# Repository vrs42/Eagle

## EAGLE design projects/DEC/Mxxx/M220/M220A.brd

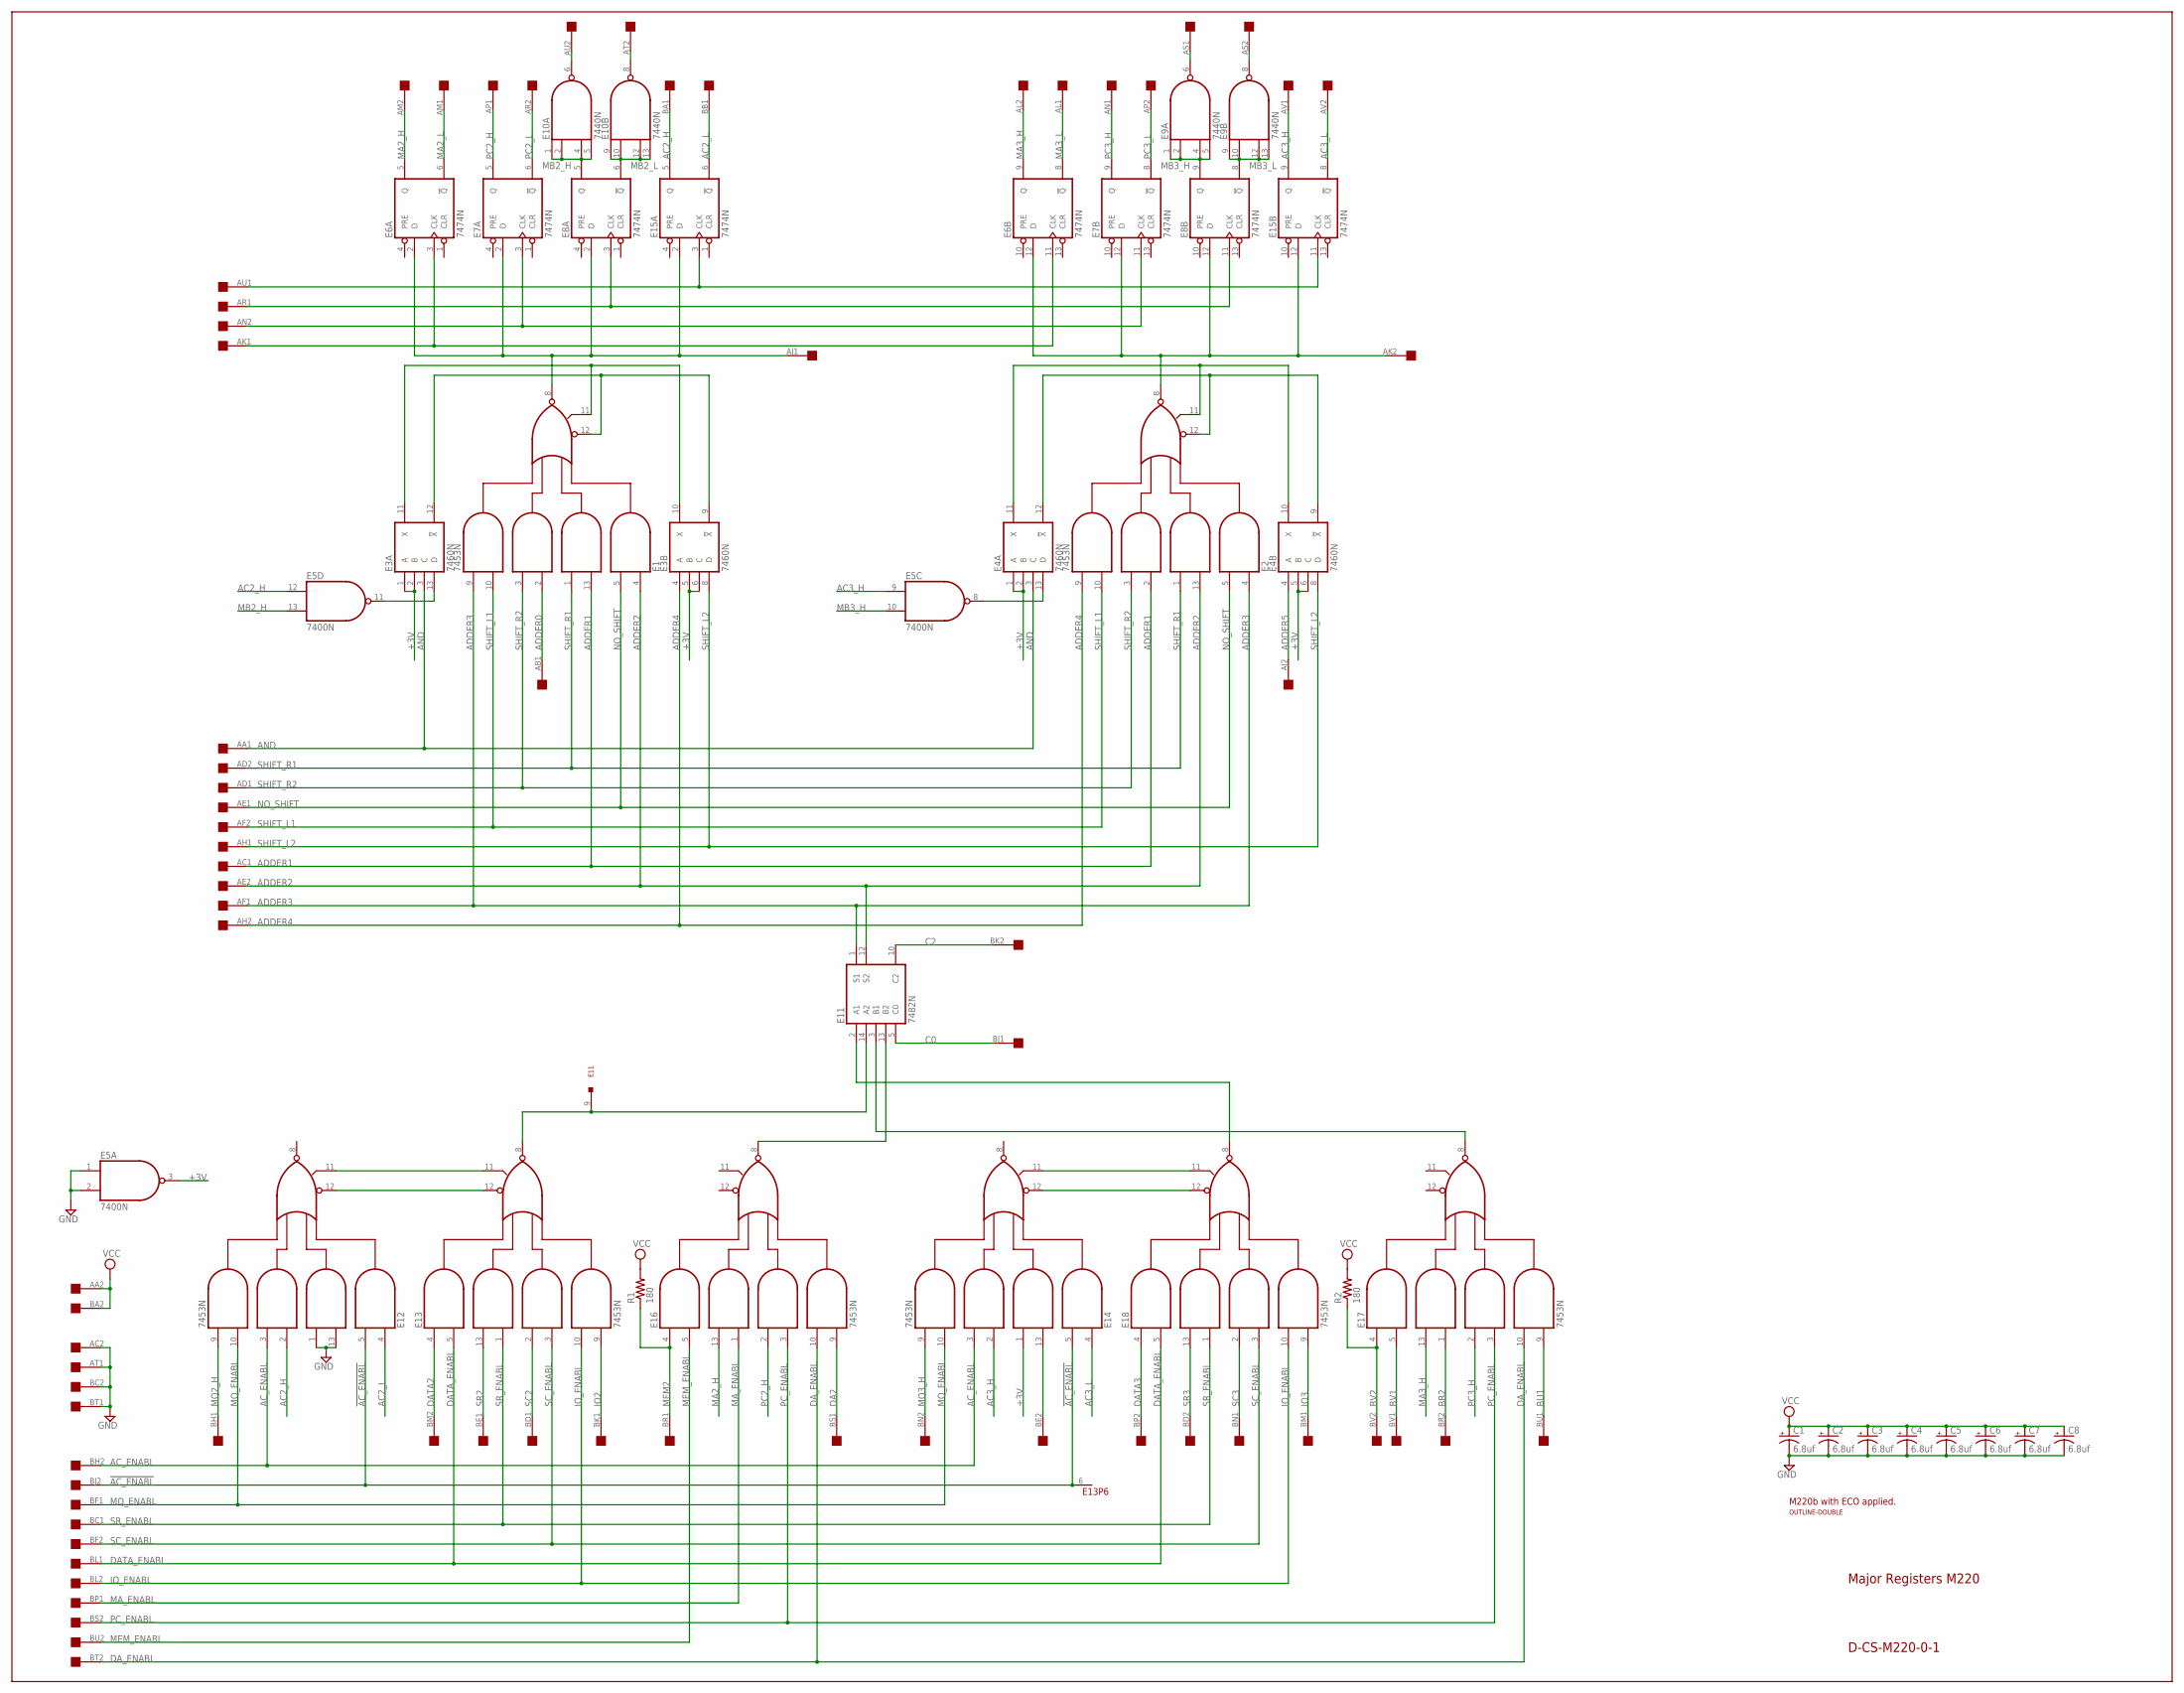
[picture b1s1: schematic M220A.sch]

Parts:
C1, C2, C3, C4, C5, C6, C7, C8: 6.8uf; E15-5
E1, E2, E12, E13, E14, E16, E17, E18: 7453N; DIL14
E3, E4: 7460N; DIL14
E5: 7400N; DIL14
E6, E7, E8, E15: 7474N; DIL14
E9, E10: 7440N; DIL14
E11: 7482N; DIL14
R1, R2: 180; 0207/10
U$1: DOUBLE; EDGE-CON4
U$2: OUTLINE-DOUBLE; DOUBLE

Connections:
!AC_ENABL: E12.5 (I2), E13.6 (SPARE), E14.5 (I2), U$1.BJ2
+3V: E3.1 (A), E3.2 (B), E3.5 (B), E3.6 (C), E4.1 (A), E4.2 (B), E4.5 (B), E4.6 (C), E5.3 (O), E14.1 (I4)
AC2_H: E5.12 (I0), E12.2 (I5), E15.5 (Q), U$1.BA1
AC2_L: E12.4 (I1), E15.6 (!Q), U$1.BB1
AC3_H: E5.9 (I0), E14.2 (I5), E15.9 (Q), U$1.AV1
AC3_L: E14.4 (I1), E15.8 (!Q), U$1.AV2
AC_ENABL: E12.3 (I6), E14.3 (I6), U$1.BH2
ADDER0: E1.2 (I5), U$1.AB1
ADDER1: E1.13 (I3), E2.2 (I5), U$1.AC1
ADDER2: E1.4 (I1), E2.13 (I3), E11.12 (S2), U$1.AE2
ADDER3: E1.9 (I8), E2.4 (I1), E11.1 (S1), U$1.AF1
ADDER4: E2.9 (I8), E3.4 (A), U$1.AH2
ADDER5: E4.4 (A), U$1.AJ2
AJ1: E1.8 (O), E6.2 (D), E7.2 (D), E8.2 (D), E15.2 (D), U$1.AJ1
AK1: E6.3 (CLK), E6.11 (CLK), U$1.AK1
AK2: E2.8 (O), E6.12 (D), E7.12 (D), E8.12 (D), E15.12 (D), U$1.AK2
AN2: E7.3 (CLK), E7.11 (CLK), U$1.AN2
AND: E3.3 (C), E4.3 (C), U$1.AA1
AR1: E8.3 (CLK), E8.11 (CLK), U$1.AR1
AS2: E9.8 (O), U$1.AS2
AT2: E10.8 (O), U$1.AT2
AU1: E15.3 (CLK), E15.11 (CLK), U$1.AU1
AU2: E10.6 (O), U$1.AU2
BE2: E14.13 (I3), U$1.BE2
BR2: E17.1 (I4), U$1.BR2
BU1: E17.9 (I8), U$1.BU1
BV1: E17.5 (I2), U$1.BV1
BV2: E17.4 (I1), R2.1, U$1.BV2
C0: E11.5 (C0), U$1.BJ1
C2: E11.10 (C2), U$1.BK2
DA2: E16.9 (I8), U$1.BS1
DATA2: E13.4 (I1), U$1.BM2
DATA3: E18.4 (I1), U$1.BP2
DATA_ENABL: E13.5 (I2), E18.5 (I2), U$1.BL1
DA_ENABL: E16.10 (I7), E17.10 (I7), U$1.BT2
GND: C1.-, C2.-, C3.-, C4.-, C5.-, C6.-, C7.-, C8.-, E1.7 (GND), E2.7 (GND), E3.7 (GND), E4.7 (GND), E5.1 (I0), E5.2 (I1), E5.7 (GND), E6.7 (GND), E7.7 (GND), E8.7 (GND), E9.7 (GND), E10.7 (GND), E11.11 (GND), E12.1 (I4), E12.7 (GND), E12.13 (I3), E13.7 (GND), E14.7 (GND), E15.7 (GND), E16.7 (GND), E17.7 (GND), E18.7 (GND), U$1.AC2, U$1.AT1, U$1.BC2, U$1.BT1
IO2: E13.9 (I8), U$1.BK1
IO3: E18.9 (I8), U$1.BM1
IO_ENABL: E13.10 (I7), E18.10 (I7), U$1.BL2
MA2_H: E6.5 (Q), E16.13 (I3), U$1.AM2
MA2_L: E6.6 (!Q), U$1.AM1
MA3_H: E6.9 (Q), E17.13 (I3), U$1.AL2
MA3_L: E6.8 (!Q), U$1.AL1
MA_ENABL: E16.1 (I4), U$1.BP1
MB2_H: E5.13 (I1), E8.5 (Q), E10.1 (I0), E10.2 (I1), E10.4 (I2), E10.5 (I3)
MB2_L: E8.6 (!Q), E10.9 (I0), E10.10 (I1), E10.12 (I2), E10.13 (I3)
MB3_H: E5.10 (I1), E8.9 (Q), E9.1 (I0), E9.2 (I1), E9.4 (I2), E9.5 (I3)
MB3_L: E8.8 (!Q), E9.9 (I0), E9.10 (I1), E9.12 (I2), E9.13 (I3)
MEM2: E16.4 (I1), R1.1, U$1.BR1
MEM_ENABL: E16.5 (I2), U$1.BU2
MQ2_H: E12.9 (I8), U$1.BH1
MQ3_H: E14.9 (I8), U$1.BN2
MQ_ENABL: E12.10 (I7), E14.10 (I7), U$1.BF1
unnamed: E3.13 (D), E5.11 (O)
unnamed: E14.12 (I9), E18.12 (I9)
unnamed: E4.13 (D), E5.8 (O)
unnamed: E14.11 (I10), E18.11 (I10)
unnamed: E11.9, E11.14 (A2), E13.8 (O)
unnamed: E12.11 (I10), E13.11 (I10)
unnamed: E12.12 (I9), E13.12 (I9)
unnamed: E11.2 (A1), E18.8 (O)
unnamed: E2.12 (I9), E4.9 (!X), E4.12 (!X)
unnamed: E1.12 (I9), E3.9 (!X), E3.12 (!X)
unnamed: E2.11 (I10), E4.10 (X), E4.11 (X)
unnamed: E11.13 (B2), E16.8 (O)
unnamed: E1.11 (I10), E3.10 (X), E3.11 (X)
unnamed: E11.3 (B1), E17.8 (O)
unnamed: E9.6 (O), U$1.AS1
NO_SHIFT: E1.5 (I2), E2.5 (I2), U$1.AE1
PC2_H: E7.5 (Q), E16.2 (I5), U$1.AP1
PC2_L: E7.6 (!Q), U$1.AR2
PC3_H: E7.9 (Q), E17.2 (I5), U$1.AN1
PC3_L: E7.8 (!Q), U$1.AP2
PC_ENABL: E16.3 (I6), E17.3 (I6), U$1.BS2
SC2: E13.2 (I5), U$1.BD1
SC3: E18.2 (I5), U$1.BN1
SC_ENABL: E13.3 (I6), E18.3 (I6), U$1.BF2
SHIFT_L1: E1.10 (I7), E2.10 (I7), U$1.AF2
SHIFT_L2: E3.8 (D), E4.8 (D), U$1.AH1
SHIFT_R1: E1.1 (I4), E2.1 (I4), U$1.AD2
SHIFT_R2: E1.3 (I6), E2.3 (I6), U$1.AD1
SR2: E13.13 (I3), U$1.BE1
SR3: E18.13 (I3), U$1.BD2
SR_ENABL: E13.1 (I4), E18.1 (I4), U$1.BC1
VCC: C1.+, C2.+, C3.+, C4.+, C5.+, C6.+, C7.+, C8.+, E1.14 (VCC), E2.14 (VCC), E3.14 (VCC), E4.14 (VCC), E5.14 (VCC), E6.14 (VCC), E7.14 (VCC), E8.14 (VCC), E9.14 (VCC), E10.14 (VCC), E11.4 (VCC), E12.14 (VCC), E13.14 (VCC), E14.14 (VCC), E15.14 (VCC), E16.14 (VCC), E17.14 (VCC), E18.14 (VCC), R1.2, R2.2, U$1.AA2, U$1.BA2

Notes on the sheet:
M220b with ECO applied.
Major Registers M220
D-CS-M220-0-1

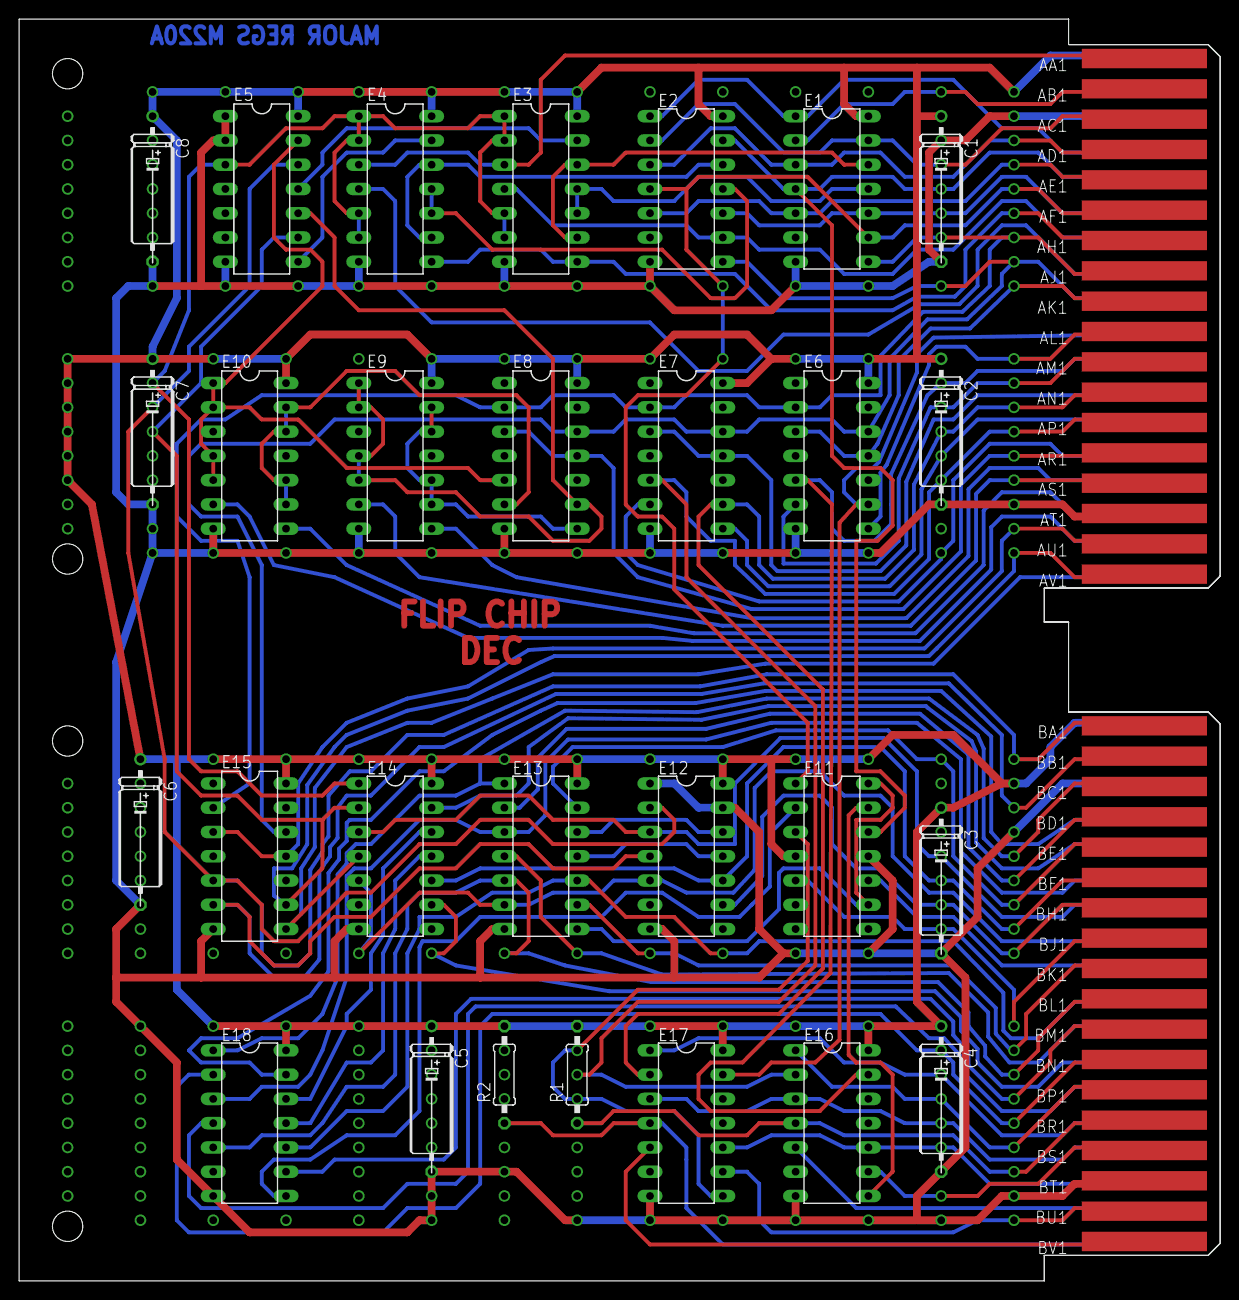
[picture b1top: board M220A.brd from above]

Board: 2 copper layers, 125.7 x 132.1 mm, 31 parts (0 on the bottom side), 85 nets.

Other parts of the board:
U$3: FLIPCHIP

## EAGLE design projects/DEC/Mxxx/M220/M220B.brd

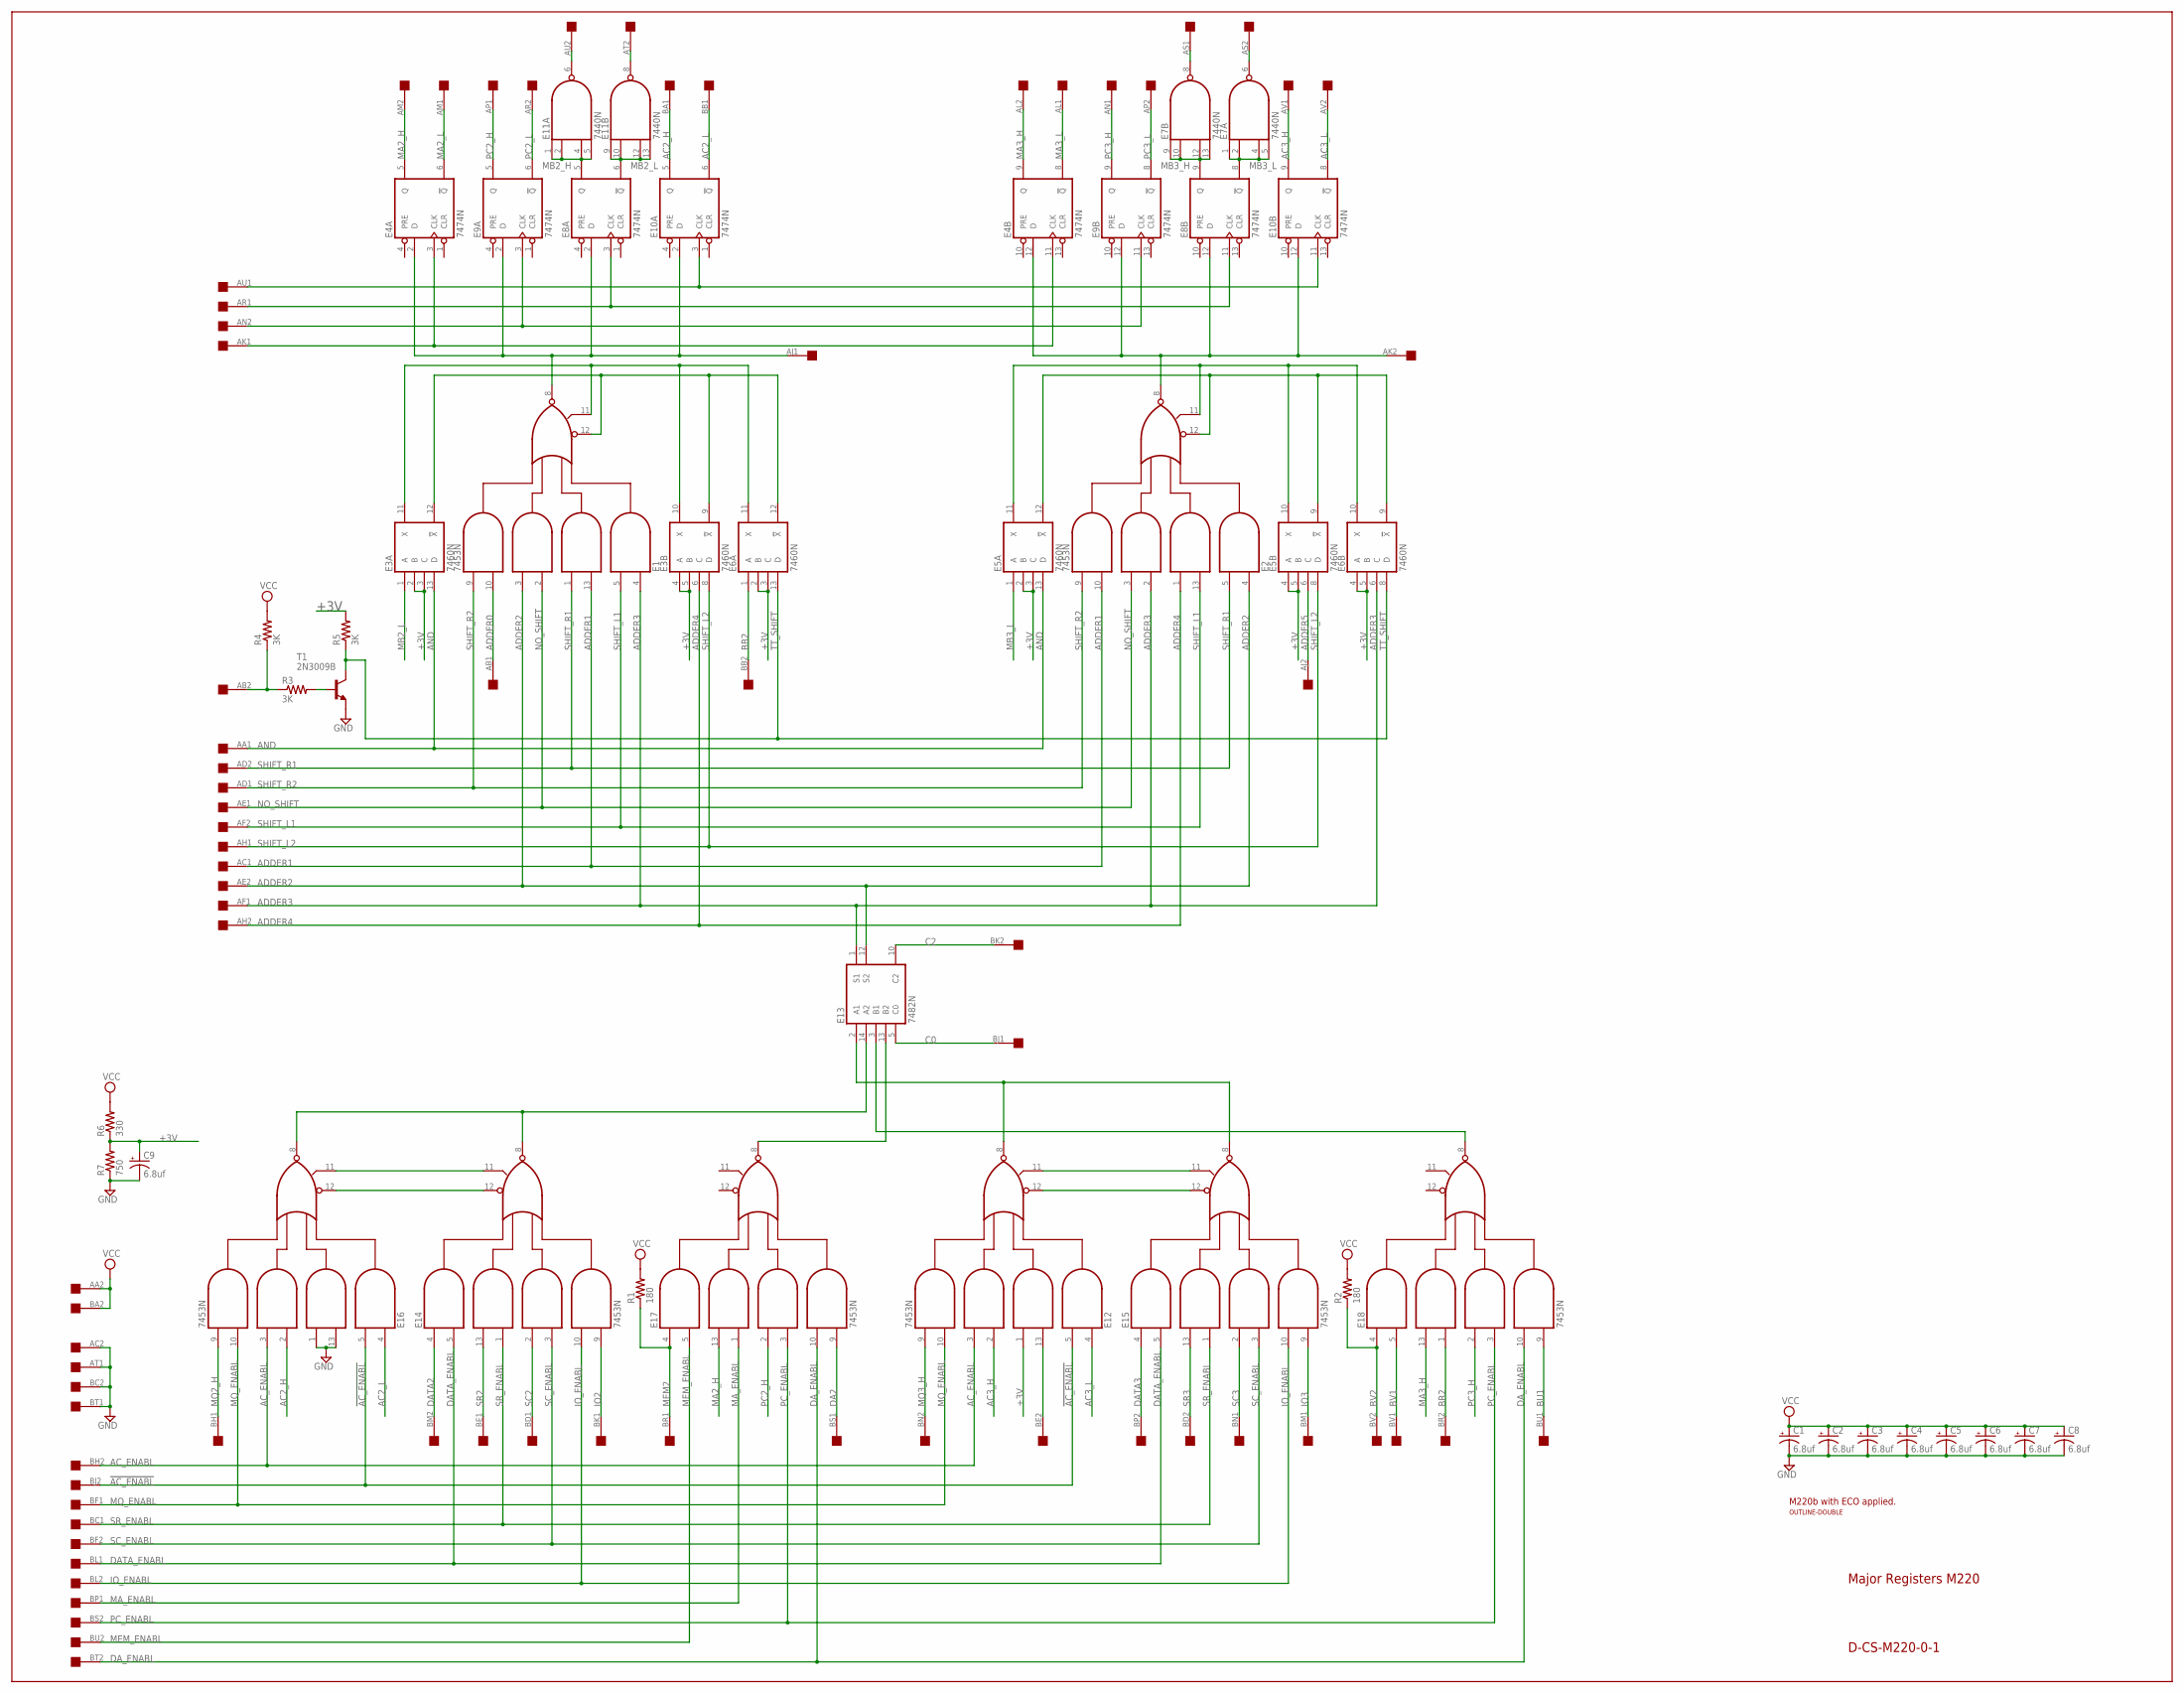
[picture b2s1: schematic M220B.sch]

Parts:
C1, C2, C3, C4, C5, C6, C7, C8, C9: 6.8uf; E15-5
E1, E2, E12, E14, E15, E16, E17, E18: 7453N; DIL14
E3, E5, E6: 7460N; DIL14
E4, E8, E9, E10: 7474N; DIL14
E7, E11: 7440N; DIL14
E13: 7482N; DIL14
R1, R2: 180; 0207/10
R3, R4, R5: 3K; 0207/10
R6: 330; 0207/10
R7: 750; 0207/10
T1: 2N3009B; TO5
U$1: DOUBLE; EDGE-CON4
U$2: OUTLINE-DOUBLE; DOUBLE

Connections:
!AC_ENABL: E12.5 (I2), E16.5 (I2), U$1.BJ2
!TT_SHIFT: R3.1, R4.1, U$1.AB2
+3V: C9.+, E3.2 (B), E3.3 (C), E3.4 (A), E3.5 (B), E5.2 (B), E5.3 (C), E5.4 (A), E5.5 (B), E6.2 (B), E6.3 (C), E6.4 (A), E6.5 (B), E12.1 (I4), R5.2, R6.1, R7.2
AC2_H: E10.5 (Q), E16.2 (I5), U$1.BA1
AC2_L: E10.6 (!Q), E16.4 (I1), U$1.BB1
AC3_H: E10.9 (Q), E12.2 (I5), U$1.AV1
AC3_L: E10.8 (!Q), E12.4 (I1), U$1.AV2
AC_ENABL: E12.3 (I6), E16.3 (I6), U$1.BH2
ADDER0: E1.10 (I7), U$1.AB1
ADDER1: E1.13 (I3), E2.10 (I7), U$1.AC1
ADDER2: E1.3 (I6), E2.4 (I1), E13.12 (S2), U$1.AE2
ADDER3: E1.4 (I1), E2.2 (I5), E6.6 (C), E13.1 (S1), U$1.AF1
ADDER4: E2.1 (I4), E3.6 (C), U$1.AH2
ADDER5: E5.6 (C), U$1.AJ2
AJ1: E1.8 (O), E4.2 (D), E8.2 (D), E9.2 (D), E10.2 (D), U$1.AJ1
AK1: E4.3 (CLK), E4.11 (CLK), U$1.AK1
AK2: E2.8 (O), E4.12 (D), E8.12 (D), E9.12 (D), E10.12 (D), U$1.AK2
AN2: E9.3 (CLK), E9.11 (CLK), U$1.AN2
AND: E3.13 (D), E5.13 (D), U$1.AA1
AR1: E8.3 (CLK), E8.11 (CLK), U$1.AR1
AS1: E7.8 (O), U$1.AS1
AS2: E7.6 (O), U$1.AS2
AT2: E11.8 (O), U$1.AT2
AU1: E10.3 (CLK), E10.11 (CLK), U$1.AU1
AU2: E11.6 (O), U$1.AU2
BB2: E6.1 (A), U$1.BB2
BE2: E12.13 (I3), U$1.BE2
BR2: E18.1 (I4), U$1.BR2
BU1: E18.9 (I8), U$1.BU1
BV1: E18.5 (I2), U$1.BV1
BV2: E18.4 (I1), R2.1, U$1.BV2
C0: E13.5 (C0), U$1.BJ1
C2: E13.10 (C2), U$1.BK2
DA2: E17.9 (I8), U$1.BS1
DATA2: E14.4 (I1), U$1.BM2
DATA3: E15.4 (I1), U$1.BP2
DATA_ENABL: E14.5 (I2), E15.5 (I2), U$1.BL1
DA_ENABL: E17.10 (I7), E18.10 (I7), U$1.BT2
GND: C1.-, C2.-, C3.-, C4.-, C5.-, C6.-, C7.-, C8.-, C9.-, E1.7 (GND), E2.7 (GND), E3.7 (GND), E4.7 (GND), E5.7 (GND), E6.7 (GND), E7.7 (GND), E8.7 (GND), E9.7 (GND), E10.7 (GND), E11.7 (GND), E12.7 (GND), E13.11 (GND), E14.7 (GND), E15.7 (GND), E16.1 (I4), E16.7 (GND), E16.13 (I3), E17.7 (GND), E18.7 (GND), R7.1, T1.1 (E), U$1.AC2, U$1.AT1, U$1.BC2, U$1.BT1
IO2: E14.9 (I8), U$1.BK1
IO3: E15.9 (I8), U$1.BM1
IO_ENABL: E14.10 (I7), E15.10 (I7), U$1.BL2
MA2_H: E4.5 (Q), E17.13 (I3), U$1.AM2
MA2_L: E4.6 (!Q), U$1.AM1
MA3_H: E4.9 (Q), E18.13 (I3), U$1.AL2
MA3_L: E4.8 (!Q), U$1.AL1
MA_ENABL: E17.1 (I4), U$1.BP1
MB2_H: E8.5 (Q), E11.1 (I0), E11.2 (I1), E11.4 (I2), E11.5 (I3)
MB2_L: E3.1 (A), E8.6 (!Q), E11.9 (I0), E11.10 (I1), E11.12 (I2), E11.13 (I3)
MB3_H: E7.9 (I0), E7.10 (I1), E7.12 (I2), E7.13 (I3), E8.9 (Q)
MB3_L: E5.1 (A), E7.1 (I0), E7.2 (I1), E7.4 (I2), E7.5 (I3), E8.8 (!Q)
MEM2: E17.4 (I1), R1.1, U$1.BR1
MEM_ENABL: E17.5 (I2), U$1.BU2
MQ2_H: E16.9 (I8), U$1.BH1
MQ3_H: E12.9 (I8), U$1.BN2
MQ_ENABL: E12.10 (I7), E16.10 (I7), U$1.BF1
unnamed: E12.12 (I9), E15.12 (I9)
unnamed: R3.2, T1.2 (B)
unnamed: E12.11 (I10), E15.11 (I10)
unnamed: E13.14 (A2), E14.8 (O), E16.8 (O)
unnamed: E14.11 (I10), E16.11 (I10)
unnamed: E14.12 (I9), E16.12 (I9)
unnamed: E12.8 (O), E13.2 (A1), E15.8 (O)
unnamed: E2.12 (I9), E5.9 (!X), E5.12 (!X), E6.9 (!X)
unnamed: E1.12 (I9), E3.9 (!X), E3.12 (!X), E6.12 (!X)
unnamed: E2.11 (I10), E5.10 (X), E5.11 (X), E6.10 (X)
unnamed: E13.13 (B2), E17.8 (O)
unnamed: E1.11 (I10), E3.10 (X), E3.11 (X), E6.11 (X)
unnamed: E13.3 (B1), E18.8 (O)
NO_SHIFT: E1.2 (I5), E2.3 (I6), U$1.AE1
PC2_H: E9.5 (Q), E17.2 (I5), U$1.AP1
PC2_L: E9.6 (!Q), U$1.AR2
PC3_H: E9.9 (Q), E18.2 (I5), U$1.AN1
PC3_L: E9.8 (!Q), U$1.AP2
PC_ENABL: E17.3 (I6), E18.3 (I6), U$1.BS2
SC2: E14.2 (I5), U$1.BD1
SC3: E15.2 (I5), U$1.BN1
SC_ENABL: E14.3 (I6), E15.3 (I6), U$1.BF2
SHIFT_L1: E1.5 (I2), E2.13 (I3), U$1.AF2
SHIFT_L2: E3.8 (D), E5.8 (D), U$1.AH1
SHIFT_R1: E1.1 (I4), E2.5 (I2), U$1.AD2
SHIFT_R2: E1.9 (I8), E2.9 (I8), U$1.AD1
SR2: E14.13 (I3), U$1.BE1
SR3: E15.13 (I3), U$1.BD2
SR_ENABL: E14.1 (I4), E15.1 (I4), U$1.BC1
TT_SHIFT: E6.8 (D), E6.13 (D), R5.1, T1.3 (C)
VCC: C1.+, C2.+, C3.+, C4.+, C5.+, C6.+, C7.+, C8.+, E1.14 (VCC), E2.14 (VCC), E3.14 (VCC), E4.14 (VCC), E5.14 (VCC), E6.14 (VCC), E7.14 (VCC), E8.14 (VCC), E9.14 (VCC), E10.14 (VCC), E11.14 (VCC), E12.14 (VCC), E13.4 (VCC), E14.14 (VCC), E15.14 (VCC), E16.14 (VCC), E17.14 (VCC), E18.14 (VCC), R1.2, R2.2, R4.2, R6.2, U$1.AA2, U$1.BA2

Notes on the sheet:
M220b with ECO applied.
Major Registers M220
D-CS-M220-0-1

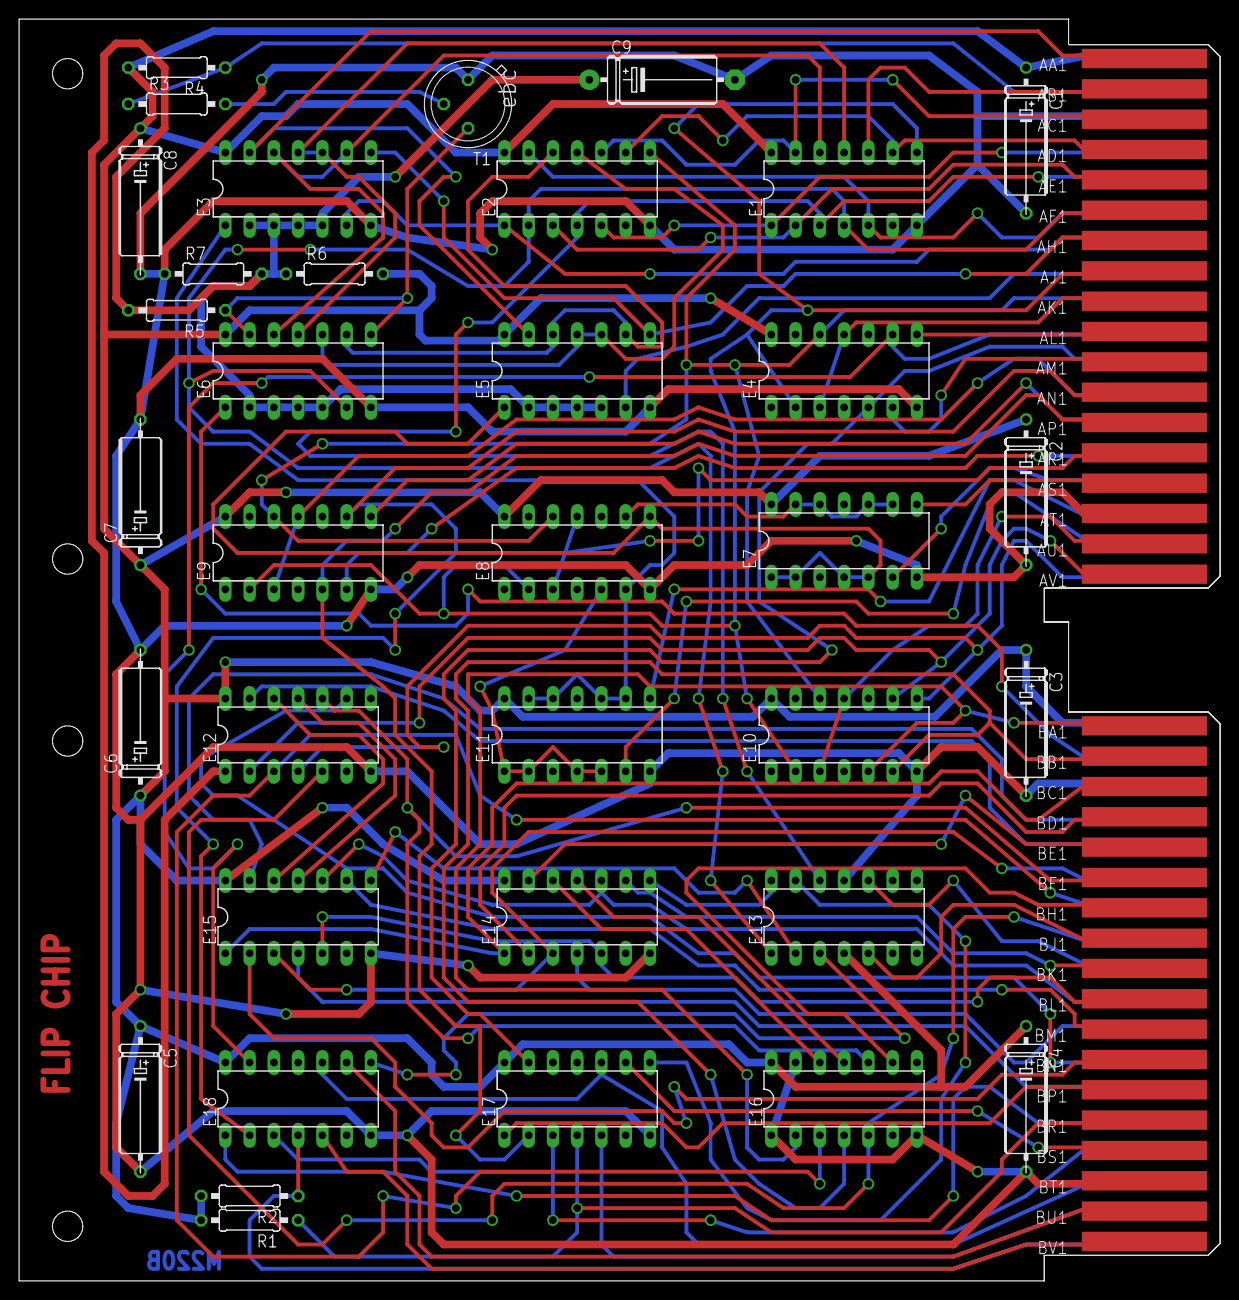
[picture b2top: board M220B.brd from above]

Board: 3 copper layers, 125.7 x 132.1 mm, 38 parts (0 on the bottom side), 87 nets.

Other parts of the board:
U$3: FLIPCHIP

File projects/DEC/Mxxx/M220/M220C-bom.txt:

Partlist exported from C:/Users/Vince/Documents/Eagle/projects/DEC/Mxxx/M220/M220C.sch at 12/9/2017 4:49:37 PM

Qty Value          Device            Package   Parts                                Description                                                     
1                  DOUBLE            EDGE-CON4 U$1                                  Double-Height DEC board                                         
2   180            R-US_0207/10      0207/10   R1, R2                               RESISTOR, American symbol                                       
1   2N3009B        2N1613            TO5       T1                                   NPN TRANSISTOR                                                  
1   330            R-US_0207/10      0207/10   R6                                   RESISTOR, American symbol                                       
3   3K             R-US_0207/10      0207/10   R3, R4, R5                           RESISTOR, American symbol                                       
9   6.8uf          CPOL-USE15-5AXIAL E15-5     C1, C2, C3, C4, C5, C6, C7, C8, C9   0.6" veresion of an electrolytic                                
2   7440N          74S20N            DIL14     E7, E11                              Dual 4-input NAND gate                                          
8   7453N          7453N             DIL14     E1, E2, E12, E14, E15, E16, E17, E18 4-2-3-2 input AND OR INVERTER gates                             
3   7460N          7460N             DIL14     E3, E5, E6                           Dual 4-input EXPANDER                                           
4   7474N          74S74N            DIL14     E4, E8, E9, E10                      Dual D type positive edge triggered FLIP FLOP, preset and clear 
1   7482N          7482N             DIL14     E13                                  2-bit binary full ADDER                                         
1   750            R-US_0207/10      0207/10   R7                                   RESISTOR, American symbol                                       
1   OUTLINE-DOUBLE OUTLINE-DOUBLE    DOUBLE    U$2                                  Board outlines for DEC boards.

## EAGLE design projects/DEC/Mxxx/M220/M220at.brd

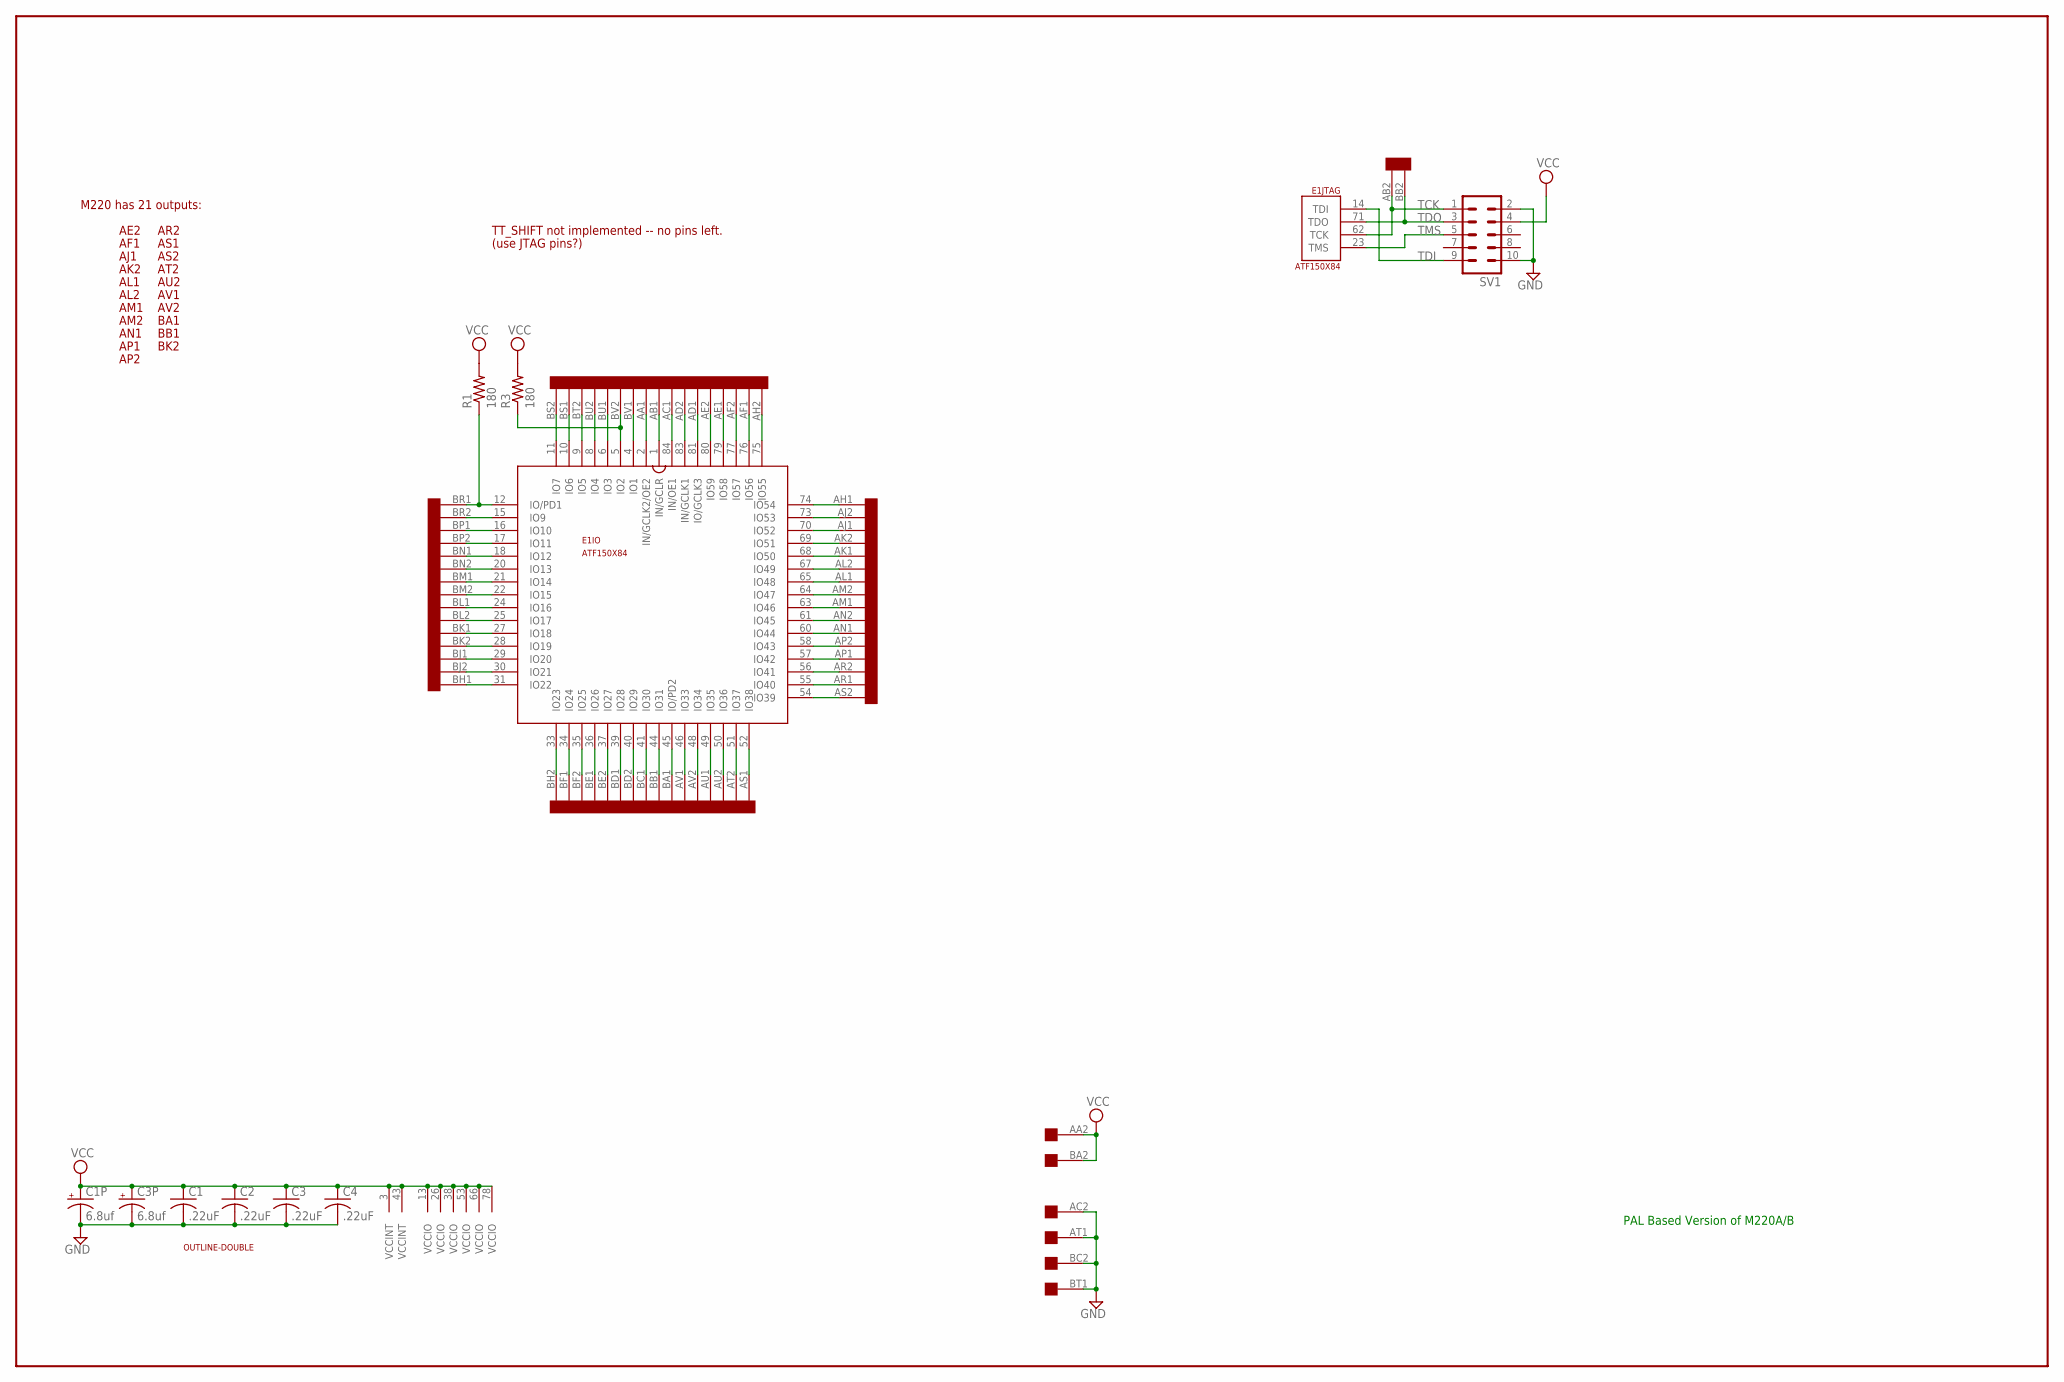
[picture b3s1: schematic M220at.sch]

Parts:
C1, C2, C3, C4: .22uF; C050-025X075
C1P, C3P: 6.8uf; E15-5
E1: ATF150X84; S84
R1, R3: 180; 0207/10
SV1: ML10
U$1: DOUBLE; EDGE-CON4
U$2: OUTLINE-DOUBLE; DOUBLE

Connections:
AA1: E1.2 (IN/GCLK2/OE2), U$1.AA1
AB1: E1.1 (IN/GCLR), U$1.AB1
AC1: E1.84 (IN/OE1), U$1.AC1
AD1: E1.81 (IO/GCLK3), U$1.AD1
AD2: E1.83 (IN/GCLK1), U$1.AD2
AE1: E1.79 (IO58), U$1.AE1
AE2: E1.80 (IO59), U$1.AE2
AF1: E1.76 (IO56), U$1.AF1
AF2: E1.77 (IO57), U$1.AF2
AH1: E1.74 (IO54), U$1.AH1
AH2: E1.75 (IO55), U$1.AH2
AJ1: E1.70 (IO52), U$1.AJ1
AJ2: E1.73 (IO53), U$1.AJ2
AK1: E1.68 (IO50), U$1.AK1
AK2: E1.69 (IO51), U$1.AK2
AL1: E1.65 (IO48), U$1.AL1
AL2: E1.67 (IO49), U$1.AL2
AM1: E1.63 (IO46), U$1.AM1
AM2: E1.64 (IO47), U$1.AM2
AN1: E1.60 (IO44), U$1.AN1
AN2: E1.61 (IO45), U$1.AN2
AP1: E1.57 (IO42), U$1.AP1
AP2: E1.58 (IO43), U$1.AP2
AR1: E1.55 (IO40), U$1.AR1
AR2: E1.56 (IO41), U$1.AR2
AS1: E1.52 (IO38), U$1.AS1
AS2: E1.54 (IO39), U$1.AS2
AT2: E1.51 (IO37), U$1.AT2
AU1: E1.49 (IO35), U$1.AU1
AU2: E1.50 (IO36), U$1.AU2
AV1: E1.46 (IO33), U$1.AV1
AV2: E1.48 (IO34), U$1.AV2
BA1: E1.45 (IO/PD2), U$1.BA1
BB1: E1.44 (IO31), U$1.BB1
BC1: E1.41 (IO30), U$1.BC1
BD1: E1.39 (IO28), U$1.BD1
BD2: E1.40 (IO29), U$1.BD2
BE1: E1.36 (IO26), U$1.BE1
BE2: E1.37 (IO27), U$1.BE2
BF1: E1.34 (IO24), U$1.BF1
BF2: E1.35 (IO25), U$1.BF2
BH1: E1.31 (IO22), U$1.BH1
BH2: E1.33 (IO23), U$1.BH2
BJ1: E1.29 (IO20), U$1.BJ1
BJ2: E1.30 (IO21), U$1.BJ2
BK1: E1.27 (IO18), U$1.BK1
BK2: E1.28 (IO19), U$1.BK2
BL1: E1.24 (IO16), U$1.BL1
BL2: E1.25 (IO17), U$1.BL2
BM1: E1.21 (IO14), U$1.BM1
BM2: E1.22 (IO15), U$1.BM2
BN1: E1.18 (IO12), U$1.BN1
BN2: E1.20 (IO13), U$1.BN2
BP1: E1.16 (IO10), U$1.BP1
BP2: E1.17 (IO11), U$1.BP2
BR1: E1.12 (IO/PD1), R1.1, U$1.BR1
BR2: E1.15 (IO9), U$1.BR2
BS1: E1.10 (IO6), U$1.BS1
BS2: E1.11 (IO7), U$1.BS2
BT2: E1.9 (IO5), U$1.BT2
BU1: E1.6 (IO3), U$1.BU1
BU2: E1.8 (IO4), U$1.BU2
BV1: E1.4 (IO1), U$1.BV1
BV2: E1.5 (IO2), R3.1, U$1.BV2
GND: C1.2, C1P.-, C2.2, C3.2, C3P.-, C4.2, E1.7 (GND), E1.19 (GND), E1.32 (GND), E1.42 (GND), E1.47 (GND), E1.59 (GND), E1.72 (GND), E1.82 (GND), SV1.2, SV1.10, U$1.AC2, U$1.AT1, U$1.BC2, U$1.BT1
TCK: E1.62 (TCK), SV1.1, U$1.AB2
TDI: E1.14 (TDI), SV1.9
TDO: E1.71 (TDO), SV1.3, U$1.BB2
TMS: E1.23 (TMS), SV1.5
VCC: C1.1, C1P.+, C2.1, C3.1, C3P.+, C4.1, E1.3 (VCCINT), E1.13 (VCCIO), E1.26 (VCCIO), E1.38 (VCCIO), E1.43 (VCCINT), E1.53 (VCCIO), E1.66 (VCCIO), E1.78 (VCCIO), R1.2, R3.2, SV1.4, U$1.AA2, U$1.BA2

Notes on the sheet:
PAL Based Version of M220A/B
M220 has 21 outputs:
AE2
BK2
AM1
AM2
AP1
AR2
AT2
AU2
BA1
BB1
AJ1
AK2
AN1
AL2
AS2
AV1
AP2
AL1
AS1
AV2
AF1
TT_SHIFT not implemented -- no pins left.
(use JTAG pins?)
